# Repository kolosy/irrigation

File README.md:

irrigation
==========

Irritgation Controller

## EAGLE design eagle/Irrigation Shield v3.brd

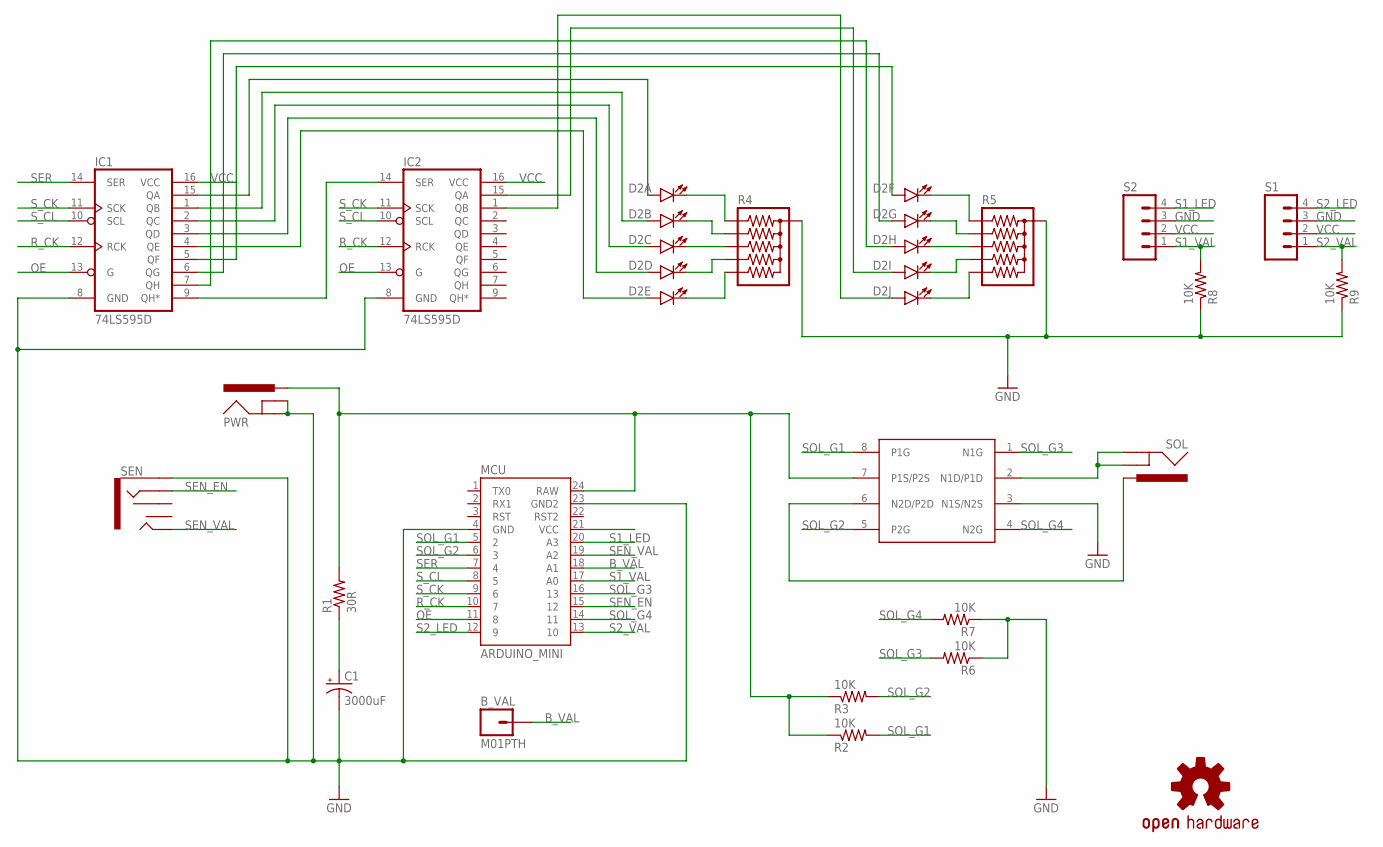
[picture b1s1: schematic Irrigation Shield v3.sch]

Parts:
B_VAL: M01PTH; 1X01
C1: 3000uF; CPOL-RADIAL-1000UF-63V
D2: LED_BARGRAPH_10; LED_BARGAPH_10
IC1, IC2: 74LS595D; SO16
LOGO1: OSHW-LOGOL; OSHW-LOGO-L
MCU: ARDUINO_MINI
PWR: POWER_JACKPTH; POWER_JACK_PTH
R1: 30R; 0603-RES
R2, R3, R6, R7, R8, R9: 10K; 0603-RES
R4, R5: RPACK-BUSSED-SIP-PTH-5; RPACK-SIP-PTH-5
S1, S2: M04PTH; 1X04
SEN: AUDIO-JACK2PTH; AUDIO-JACK
SOL: POWER_JACKPTH; POWER_JACK_PTH
U$1: ZXMHC6A07N8; SO8

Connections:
B_VAL: B_VAL.1, MCU.18 (A1)
GND: C1.2 (-), IC1.8 (GND), IC2.8 (GND), MCU.4 (GND), MCU.23 (GND2), PWR.GND, PWR.GNDBREAK, R4.P$1 (1), R5.P$1 (1), R6.1, R7.1, R8.1, R9.1, S1.3, S2.3, SEN.SLEEVE, U$1.3 (N1S/N2S)
unnamed: SOL.GND, SOL.GNDBREAK, U$1.2 (N1D/P1D)
unnamed: SOL.PWR, U$1.6 (N2D/P2D)
unnamed: IC1.9 (QH*), IC2.14 (SER)
unnamed: D2.7 (A), IC1.6 (QG)
unnamed: MCU.24 (RAW), PWR.PWR, R1.2, R2.1, R3.1, U$1.7 (P1S/P2S)
unnamed: C1.1 (+), R1.1
unnamed: D2.15 (C), R5.P$2 (2)
unnamed: D2.14 (C), R5.P$3 (3)
unnamed: D2.13 (C), R5.P$4 (4)
unnamed: D2.12 (C), R5.P$5 (5)
unnamed: D2.11 (C), R5.P$6 (6)
unnamed: D2.16 (C), R4.P$6 (6)
unnamed: D2.17 (C), R4.P$5 (5)
unnamed: D2.18 (C), R4.P$4 (4)
unnamed: D2.19 (C), R4.P$3 (3)
unnamed: D2.20 (C), R4.P$2 (2)
unnamed: D2.1 (A), IC1.15 (QA)
unnamed: D2.2 (A), IC1.1 (QB)
unnamed: D2.3 (A), IC1.2 (QC)
unnamed: D2.4 (A), IC1.3 (QD)
unnamed: D2.5 (A), IC1.4 (QE)
unnamed: D2.6 (A), IC1.5 (QF)
unnamed: D2.8 (A), IC1.7 (QH)
unnamed: D2.9 (A), IC2.15 (QA)
unnamed: D2.10 (A), IC2.1 (QB)
OE: IC1.13 (G), IC2.13 (G), MCU.11 (8)
R_CK: IC1.12 (RCK), IC2.12 (RCK), MCU.10 (7)
S1_LED: MCU.20 (A3), S2.4
S1_VAL: MCU.17 (A0), R8.2, S2.1
S2_LED: MCU.12 (9), S1.4
S2_VAL: MCU.13 (10), R9.2, S1.1
SEN_EN: MCU.15 (12), SEN.RING
SEN_VAL: MCU.19 (A2), SEN.TIP
SER: IC1.14 (SER), MCU.7 (4)
SOL_G1: MCU.5 (2), R2.2, U$1.8 (P1G)
SOL_G2: MCU.6 (3), R3.2, U$1.5 (P2G)
SOL_G3: MCU.16 (13), R6.2, U$1.1 (N1G)
SOL_G4: MCU.14 (11), R7.2, U$1.4 (N2G)
S_CK: IC1.11 (SCK), IC2.11 (SCK), MCU.9 (6)
S_CL: IC1.10 (SCL), IC2.10 (SCL), MCU.8 (5)
VCC: IC1.16 (VCC), IC2.16 (VCC), MCU.21 (VCC), S1.2, S2.2

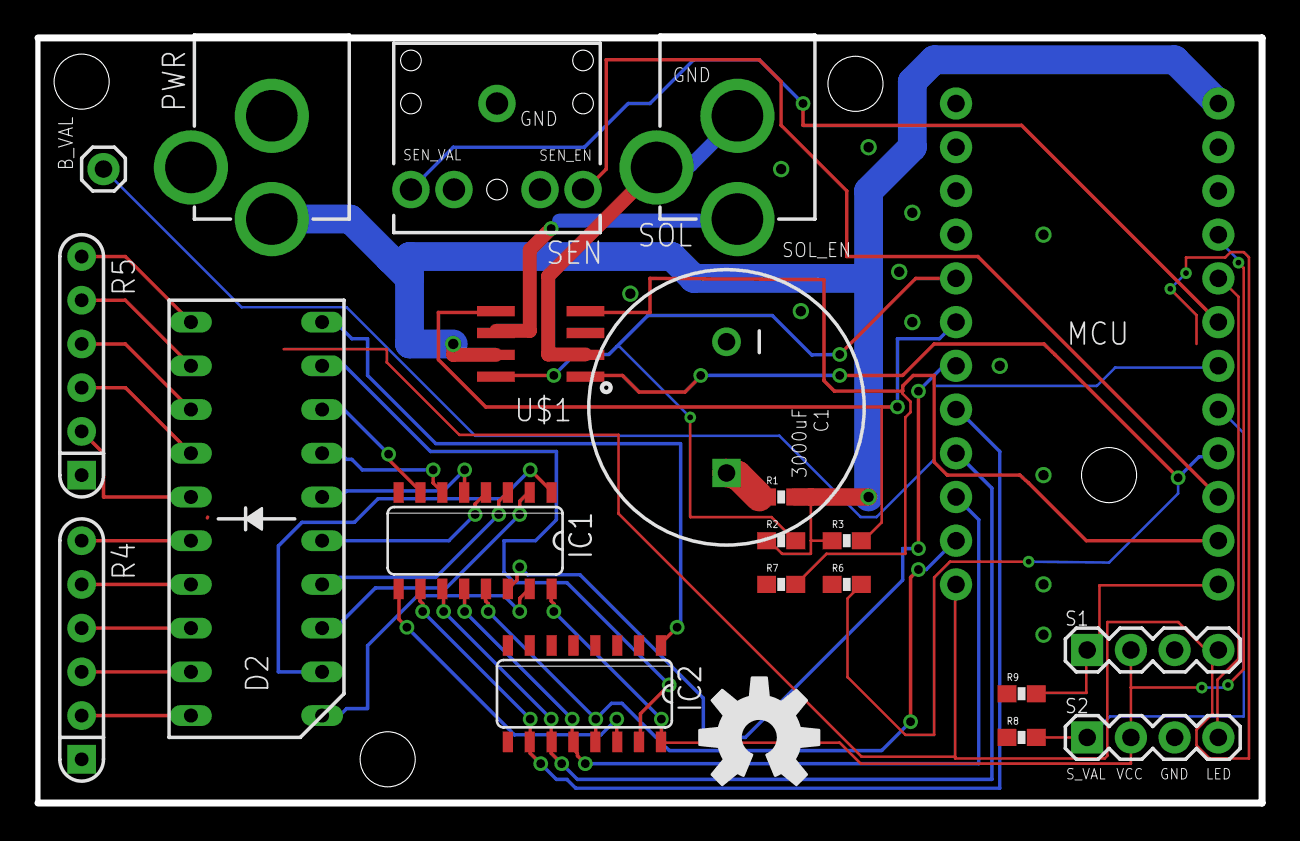
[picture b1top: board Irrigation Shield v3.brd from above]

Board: 2 copper layers, 71.1 x 44.4 mm, 22 parts (0 on the bottom side), 43 nets.

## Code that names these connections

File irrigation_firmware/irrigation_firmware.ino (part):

#include "LowPower.h"

int SER_Pin = 4;   //pin 14 on the 75HC595
int RCLK_Pin = 7;  //pin 12 on the 75HC595
int SRCLK_Pin = 6; //pin 11 on the 75HC595
int S_CL_Pin = 5;
int OE_Pin = 8;

#define SENSOR_POWER 14 // pin 12 on a pro mini
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#define N1G 15 // pin 13 on a pro mini
#define N2G 16 // pin 11 on a pro mini

#define S1_LED A3
#define S2_LED A1
#define S1_VAL A0
#define S2_VAL 10

//How many of the shift registers - change this
#define number_of_74hc595s 2 
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  delay(10);
  closeSolenoid();
  
  pinMode(SER_Pin, OUTPUT);
  pinMode(RCLK_Pin, OUTPUT);
  pinMode(SRCLK_Pin, OUTPUT);
  pinMode(OE_Pin, OUTPUT);
  pinMode(S_CL_Pin, OUTPUT);
  
  pinMode(S1_LED, OUTPUT);
  pinMode(S1_VAL, INPUT);

  pinMode(S2_LED, OUTPUT);
  pinMode(S2_VAL, INPUT);
  
  pinMode(SENSOR_POWER, OUTPUT);
  
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  
  delay(10);
  digitalWrite(OE_Pin, LOW);
  digitalWrite(S_CL_Pin, HIGH);

  day_millis = MINUTE * 60L * 24L;
  water_today = 0;
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
    int val = registers[i];

    digitalWrite(SER_Pin, val);
    digitalWrite(SRCLK_Pin, HIGH);

  }
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
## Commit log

2014-05-03 initial load

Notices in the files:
parts and their libraries:
SparkFun: Licensing: CC v3.0 Share-Alike You are welcome to use this library for commercial purposes.
